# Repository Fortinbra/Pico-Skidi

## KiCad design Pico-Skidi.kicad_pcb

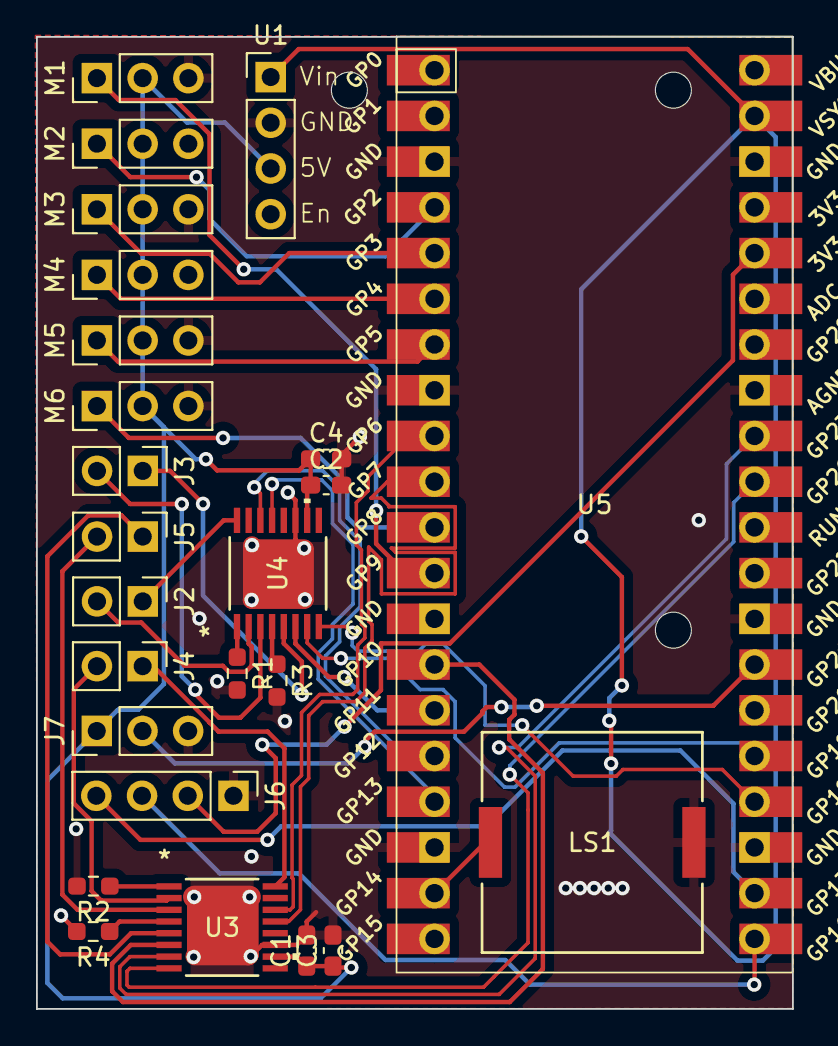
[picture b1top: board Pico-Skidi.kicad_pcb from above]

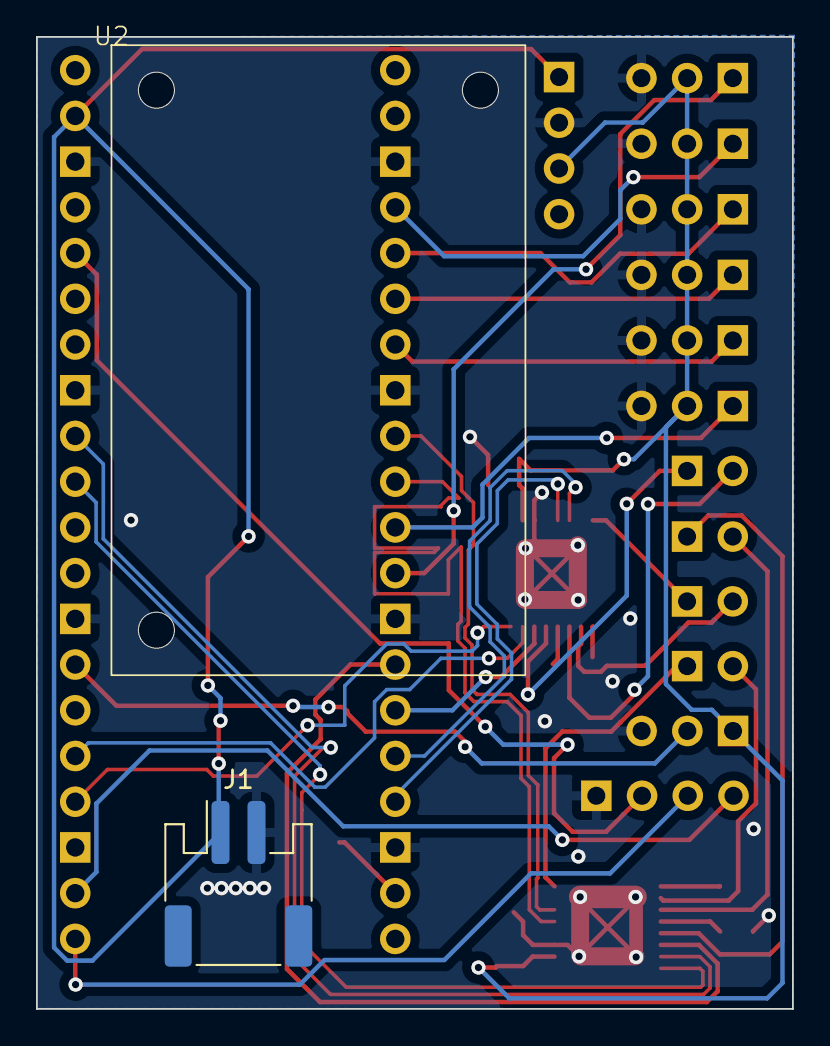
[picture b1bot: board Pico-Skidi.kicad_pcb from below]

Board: 2 copper layers, 42.0 x 54.0 mm, 27 parts (2 on the bottom side), 36 nets.

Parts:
C1, C2, C3, C4: C; C_0603_1608Metric_Pad1.08x0.95mm_HandSolder
J1: Conn_01x02; JST_PH_S2B-PH-SM4-TB_1x02-1MP_P2.00mm_Horizontal
J2: Motor 3; PinHeader_1x02_P2.54mm_Vertical
J3: Motor 4; PinHeader_1x02_P2.54mm_Vertical
J4: Motor 1; PinHeader_1x02_P2.54mm_Vertical
J5: Motor 2; PinHeader_1x02_P2.54mm_Vertical
J6: Conn_01x04; PinHeader_1x04_P2.54mm_Vertical
J7: RGBLED; PinHeader_1x03_P2.54mm_Vertical
LS1: PKLCS1212E4001-R1; PKLCS_472x472_MUR
M1, M2, M3, M4, M5, M6: Motor_Servo; PinHeader_1x03_P2.54mm_Vertical
R1, R2, R3, R4: R; R_0603_1608Metric_Pad0.98x0.95mm_HandSolder
U1: TPS61023
U2: Pimoroni Amigo Pro Mounts
U3, U4: PDRV8411PWPR; TSSOP_11PWPR_TEX
U5: Pico; RPi_Pico_TH

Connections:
+3.3V: J6.2, U5.36 (3V3)
+5V: C1.1, C2.1, C3.1, C4.1, J7.1, M1.2 (+), M2.2 (+), M3.2 (+), M4.2 (+), M5.2 (+), M6.2 (+), U1.3 (5v), U3.10 (VM), U4.10 (VM)
/Extras/BUZZER: LS1.1, U5.19 (GPIO14)
/Extras/RGB_LED: J7.2, U5.27 (GPIO21)
/Motor Management/MOT_A+: U3.14 (AIN1), U5.9 (GPIO6)
/Motor Management/MOT_A-: U3.13 (AIN2), U5.10 (GPIO7)
/Motor Management/MOT_B+: U3.7 (BIN1), U5.32 (GPIO27_ADC1)
/Motor Management/MOT_B-: U3.8 (BIN2), U5.31 (GPIO26_ADC0)
/Motor Management/MOT_C+: U4.14 (AIN1), U5.16 (GPIO12)
/Motor Management/MOT_C-: U4.13 (AIN2), U5.17 (GPIO13)
/Motor Management/MOT_D+: U4.7 (BIN1), U5.25 (GPIO19)
/Motor Management/MOT_D-: U4.8 (BIN2), U5.24 (GPIO18)
/Motor Management/nFAULT_01: U3.6 (nFAULT), U5.14 (GPIO10)
/Motor Management/nFAULT_02: U4.6 (nFAULT), U5.15 (GPIO11)
/Pico W/SCL: J6.4, U5.22 (GPIO17)
/Pico W/SDA: J6.3, U5.21 (GPIO16)
/Pico W/SRV_01: M2.1 (PWM), U5.4 (GPIO2)
/Pico W/SRV_02: M3.1 (PWM), U5.5 (GPIO3)
/Pico W/SRV_03: M4.1 (PWM), U5.6 (GPIO4)
/Pico W/SRV_04: M5.1 (PWM), U5.7 (GPIO5)
/Pico W/SRV_05: M6.1 (PWM), U5.11 (GPIO8)
/Pico W/SRV_06: M1.1 (PWM), U5.12 (GPIO9)
GND: C1.2, C2.2, C3.2, C4.2, J1.2, J6.1, J7.3, LS1.2, M1.3 (-), M2.3 (-), M3.3 (-), M4.3 (-), M5.3 (-), M6.3 (-), R1.2, R2.2, R3.2, R4.2, U1.2 (GND), U3.11 (GND), U3.EPAD, U4.11 (GND), U4.EPAD, U5.3 (GND), U5.8 (GND), U5.13 (GND), U5.18 (GND), U5.23 (GND), U5.28 (GND), U5.33 (AGND), U5.38 (GND)
unnamed: J2.1, U4.16 (AOUT1)
unnamed: J2.2, U4.2 (AOUT2)
unnamed: J3.1, U4.5 (BOUT1)
unnamed: J3.2, U4.3 (BOUT2)
unnamed: J4.1, U3.16 (AOUT1)
unnamed: J4.2, U3.2 (AOUT2)
unnamed: J5.1, U3.5 (BOUT1)
unnamed: J5.2, U3.3 (BOUT2)
unnamed: R2.1, U3.1 (AISEN)
unnamed: R4.1, U3.4 (BISEN)
unnamed: R1.1, U4.1 (AISEN)
unnamed: R3.1, U4.4 (BISEN)
VSYS: J1.1, U1.1 (VIN), U5.39 (VSYS)

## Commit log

2023-09-25 cleanup
2023-09-25 Adding pico board
2023-09-25 Starting on Power
2023-10-23 Sync
2023-10-23 Additional sheets in the schematic
2023-10-23 Adding pins for Pico
2023-10-29 Lots of changes
2023-12-09 syncing
2023-12-09 progress at last
2023-12-11 Adding Power
2023-12-11 Routed, now just silk screens left
